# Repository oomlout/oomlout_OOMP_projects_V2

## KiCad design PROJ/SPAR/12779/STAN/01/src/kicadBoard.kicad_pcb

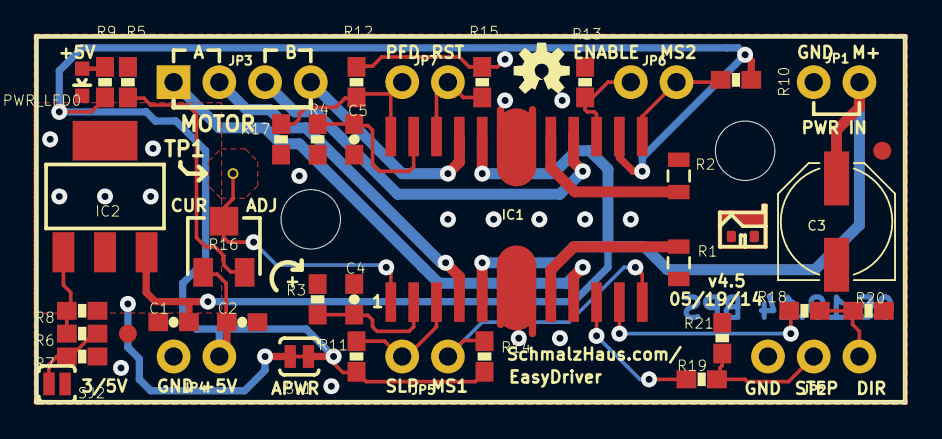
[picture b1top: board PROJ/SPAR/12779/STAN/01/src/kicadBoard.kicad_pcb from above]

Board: 2 copper layers, 48.3 x 20.3 mm, 47 parts (1 on the bottom side), 27 nets.

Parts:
C1: .1uF; 0603-CAP
C2: 1uf; 0603-CAP
C3: 47uF; PANASONIC_D
C4, C5: 680pF; 0603-CAP
FID1, FID2: FIDUCIAL1X2; FIDUCIAL-1X2
FRAME2: FRAME-LETTER; CREATIVE_COMMONS
IC1: A3967SLB; SO24W
IC2: V_REG_317SMD; SOT223
JP1, JP4, JP5, JP6, JP7: 1X02_NO_SILK
JP2: 1X03_NO_SILK
JP3: 1X04_NO_SILK
JP8, JP9: STAND-OFF
LOGO1: OSHW-LOGOS; OSHW-LOGO-S
PWR_LED0: YELLOW; LED-0603
R1, R2: .75; 0805
R3, R4: 20K; 0603-RES
R5: 2.49K; 0603-RES
R6: 390; 0603-RES
R7: 330; 0603-RES
R8: 240; 0603-RES
R9, R18, R19: 1K; 0603-RES
R10, R11, R12, R13, R14, R15, R20, R21: 10K; 0603-RES
R16: 10K; TRIMPOT-3MM-2
R17: 6.8K; 0603-RES
SJ1: SOLDERJUMPERTRACE; SJ_2S-TRACE
SJ2: SOLDERJUMPERNO; SJ_2S-NO
TP1: TEST-POINTTP_15TH_THRU; TP_15TH
U$1: SCHMALZHAUS_SMALL
U$2: LOGO-SFENEW; SFE-NEW-WEBLOGO

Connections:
5V_ALT: IC2.2, IC2.4, R8.2, SJ1.1
DIR: IC1.11, R18.1
DIR_IN: JP2.3, R18.2, R20.2
ENABLE: IC1.15, JP6.1, R13.2
GND: C1.2, C2.2, C3.-, C4.2, C5.2, IC1.6, IC1.7, IC1.18, IC1.19, JP1.1, JP2.1, JP4.2, PWR_LED0.C, R1.1, R2.1, R3.1, R4.1, R5.1, R7.1, R13.1, R17.1, R20.1, R21.1, SJ2.2
MS1: IC1.12, JP5.1, R14.1
MS2: IC1.13, JP6.2, R10.1
unnamed: IC1.8, R1.2
unnamed: PWR_LED0.A, R9.1
unnamed: IC1.17, R2.2
unnamed: R6.1, R7.2, SJ2.1
unnamed: C4.1, IC1.2, R3.2
unnamed: IC2.1, R6.2, R8.1
unnamed: C5.1, IC1.23, R4.2
unnamed: R5.2, R16.3
OUT1A: IC1.16, JP3.3
OUT1B: IC1.21, JP3.4
OUT2A: IC1.9, JP3.1
OUT2B: IC1.4, JP3.2
PFD: IC1.24, JP7.1, R12.1, R17.2
RESET: IC1.22, JP7.2, R15.1
SLEEP: IC1.3, JP5.2, R11.1
STEP: IC1.10, R19.1
STEP_IN: JP2.2, R19.2, R21.2
V+: C1.1, C3.+, IC1.5, IC1.20, IC2.3, JP1.2
VCC: C2.1, IC1.14, JP4.1, R9.2, R10.2, R11.2, R12.2, R14.2, R15.2, R16.1, SJ1.2
VREF: IC1.1, R16.2, TP1.P$1

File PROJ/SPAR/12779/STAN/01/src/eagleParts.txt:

Partlist

Exported from boardEagle.brd at 18/08/2022 15:58

EAGLE Version 9.6.2 Copyright (c) 1988-2020 Autodesk, Inc.

Assembly variant: 

Part     Value                  Package       Library                    Position (inch)       Orientation

C1       .1uF                   0603-CAP      SparkFun-Capacitors        (0.3 0.175)           R180
C2       1uf                    0603-CAP      SparkFun-Capacitors        (0.45 0.175)          R0
C3       47uF                   PANASONIC_D   rcl                        (1.75 0.395)          R90
C4       680pF                  0603-CAP      SparkFun-Capacitors        (0.695 0.225)         R90
C5       680pF                  0603-CAP      SparkFun-Capacitors        (0.695 0.575)         R270
FID1     FIDUCIAL1X2            FIDUCIAL-1X2  SparkFun-Aesthetics        (1.85 0.55)           R0
FID2     FIDUCIAL1X2            FIDUCIAL-1X2  SparkFun-Aesthetics        (0.2 0.15)            R0
IC1      A3967SLB               SO24W         Allegro                    (1.05 0.4)            R0
IC2      V_REG_317SMD           SOT223        SparkFun03_30_09           (0.15 0.45)           R0
JP1                             1X02_NO_SILK  SparkFun                   (1.7 0.7)             R0
JP2                             1X03_NO_SILK  SparkFun                   (1.6 0.1)             R0
JP3                             1X04_NO_SILK  SparkFun                   (0.3 0.7)             R0
JP4                             1X02_NO_SILK  SparkFun                   (0.4 0.1)             R180
JP5                             1X02_NO_SILK  SparkFun                   (0.9 0.1)             R180
JP6                             1X02_NO_SILK  SparkFun                   (1.3 0.7)             R0
JP7                             1X02_NO_SILK  SparkFun                   (0.8 0.7)             R0
PWR_LED  YELLOW                 LED-0603      SparkFun-LED               (0.1 0.7)             R180
R1       .75                    0805          SparkFun-Resistors         (1.405 0.305)         R90
R2       .75                    0805          SparkFun-Resistors         (1.405 0.495)         R270
R3       20K                    0603-RES      SparkFun-Resistors         (0.615 0.225)         R270
R4       20K                    0603-RES      SparkFun-Resistors         (0.615 0.575)         R90
R5       2.49K                  0603-RES      SparkFun-Resistors         (0.2 0.7)             R270
R6       390                    0603-RES      SparkFun-Resistors         (0.1 0.15)            R180
R7       330                    0603-RES      SparkFun-Resistors         (0.1 0.1)             R180
R8       240                    0603-RES      SparkFun-Resistors         (0.1 0.2)             R0
R9       1K                     0603-RES      SparkFun-Resistors         (0.15 0.7)            R270
R10      10K                    0603-RES      SparkFun-Resistors         (1.53 0.705)          R0
R11      10K                    0603-RES      SparkFun-Resistors         (0.7 0.1)             R270
R12      10K                    0603-RES      SparkFun-Resistors         (0.7 0.7)             R90
R13      10K                    0603-RES      SparkFun-Resistors         (1.2 0.7)             R270
R14      10K                    0603-RES      SparkFun-Resistors         (0.98 0.1)            R270
R15      10K                    0603-RES      SparkFun-Resistors         (0.975 0.7)           R90
R16      10K                    TRIMPOT-3MM-2 SparkFun-Electromechanical (0.41 0.34)           R0
R17      6.8K                   0603-RES      SparkFun-Resistors         (0.535 0.575)         R90
R18      1K                     0603-RES      SparkFun-Resistors         (1.68 0.2)            R0
R19      1K                     0603-RES      SparkFun-Resistors         (1.455 0.05)          R0
R20      10K                    0603-RES      SparkFun-Resistors         (1.82 0.2)            R180
R21      10K                    0603-RES      SparkFun-Resistors         (1.5 0.14)            R270
SJ1      SOLDERJUMPERTRACE      SJ_2S-TRACE   SparkFun03_30_09           (0.575 0.1)           R0
SJ2      SOLDERJUMPERNO         SJ_2S-NO      SparkFun03_30_09           (0.045 0.04)          R0
TP1      TEST-POINTTP_15TH_THRU TP_15TH       SparkFun-Passives          (0.43 0.5)            R0

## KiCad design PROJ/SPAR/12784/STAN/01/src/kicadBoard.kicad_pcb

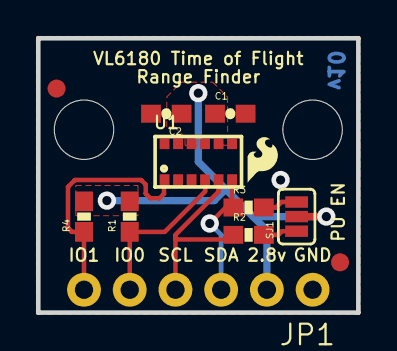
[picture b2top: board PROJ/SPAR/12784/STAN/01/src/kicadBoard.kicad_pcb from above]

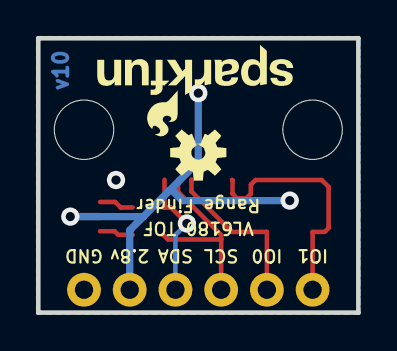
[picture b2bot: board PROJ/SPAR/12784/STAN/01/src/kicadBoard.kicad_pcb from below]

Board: 2 copper layers, 17.8 x 15.2 mm, 17 parts (2 on the bottom side), 8 nets.

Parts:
C1: 4.7uF; 0603-CAP
C2: 0.1uF; 0603-CAP
FID1, FID2: FIDUCIAL1X2; FIDUCIAL-1X2
FRAME1: FRAME-LETTER; CREATIVE_COMMONS
JP1: 1X06
LOGO1: SFE_LOGO_NAME_FLAME.1_INCH; SFE_LOGO_NAME_FLAME_.1
LOGO2: OSHW-LOGOS; OSHW-LOGO-S
R1, R4: 47K; 0603-RES
R2, R3: 2.2k; 0603-RES
SJ1: PAD-JUMPER-3-NC_BY_PASTE_YES_SILK_FULL_BOX
STANDOFF1, STANDOFF2: STAND-OFF
U1: VL6180
U$2: SFE_LOGO_FLAME_.1

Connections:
2.8V: C1.1, C2.1, JP1.2, R1.2, R4.2, SJ1.2, U1.8, U1.10
GND: C1.2, C2.2, JP1.1, U1.9, U1.12
GPIO0: JP1.5, R1.1, U1.4
GPIO1: JP1.6, R4.1, U1.1
unnamed: R2.2, SJ1.1
unnamed: R3.2, SJ1.3
SCL: JP1.4, R2.1, U1.5
SDA: JP1.3, R3.1, U1.6

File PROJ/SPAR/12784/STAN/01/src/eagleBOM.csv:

"Part";"Value";"Device";"Package";"Description";"PROD_ID";"VALUE";
"C1";"4.7uF";"4.7UF-6.3V-10%(0603)0603";"0603-CAP";"CAP-08280";"CAP-08280";"4.7uF";
"C2";"0.1uF";"0.1UF-25V(+80/-20%)(0603)";"0603-CAP";"CAP-00810";"CAP-00810";"0.1uF";
"FID1";"FIDUCIAL1X2";"FIDUCIAL1X2";"FIDUCIAL-1X2";"Fiducial Alignment Points";"";"";
"FID2";"FIDUCIAL1X2";"FIDUCIAL1X2";"FIDUCIAL-1X2";"Fiducial Alignment Points";"";"";
"FRAME1";"FRAME-LETTER";"FRAME-LETTER";"CREATIVE_COMMONS";"Schematic Frame";"";"";
"JP1";"";"M06SIP";"1X06";"Header 6";"";"";
"LOGO1";"SFE_LOGO_NAME_FLAME.1_INCH";"SFE_LOGO_NAME_FLAME.1_INCH";"SFE_LOGO_NAME_FLAME_.1";"SFE Logo, name and flame";"";"";
"LOGO2";"OSHW-LOGOS";"OSHW-LOGOS";"OSHW-LOGO-S";"Open Source Hardware Logo This logo indicates the piece of hardware it is found on incorporates a OSHW license and/or adheres to the definition of open source hardware found here: http://freedomdefined.org/OSHW";"";"";
"R1";"47K";"47KOHM1/10W1%(0603)";"0603-RES";"RES-07871";"RES-07871";"47K";
"R2";"2.2k";"2.2KOHM1/10W1%(0603)";"0603-RES";"RES-08272";"RES-08272";"2.2k";
"R3";"2.2k";"2.2KOHM1/10W1%(0603)";"0603-RES";"RES-08272";"RES-08272";"2.2k";
"R4";"47K";"47KOHM1/10W1%(0603)";"0603-RES";"RES-07871";"RES-07871";"47K";
"SJ1";"";"JUMPER-PAD-3-NC_BY_PASTE";"PAD-JUMPER-3-NC_BY_PASTE_YES_SILK_FULL_BOX";"";"";"";
"STANDOFF1";"STAND-OFF";"STAND-OFF";"STAND-OFF";"#4 Stand Off";"";"";
"STANDOFF2";"STAND-OFF";"STAND-OFF";"STAND-OFF";"#4 Stand Off";"";"";
"U1";"VL6180";"VL6180";"VL6180";"";"IC-12007";"";

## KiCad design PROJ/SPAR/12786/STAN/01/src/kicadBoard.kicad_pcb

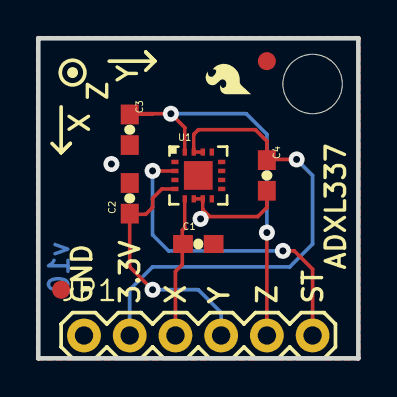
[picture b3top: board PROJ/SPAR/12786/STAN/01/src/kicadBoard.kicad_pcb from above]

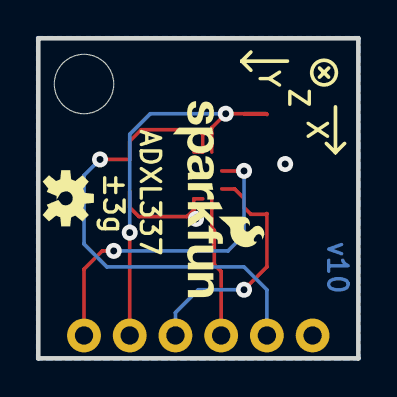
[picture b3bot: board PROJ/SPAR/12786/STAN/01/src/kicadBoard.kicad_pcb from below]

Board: 2 copper layers, 17.8 x 17.8 mm, 13 parts (2 on the bottom side), 6 nets.

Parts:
C1, C2, C3: 10nF; 0603-CAP
C4: 0.1uF; 0603-CAP
FID1, FID2: FIDUCIAL1X2; FIDUCIAL-1X2
FRAME1: FRAME-LETTER; CREATIVE_COMMONS
JP1: 1X06
LOGO1: SFE_LOGO_FLAME.1_INCH; SFE_LOGO_FLAME_.1
LOGO2: OSHW-LOGOS; OSHW-LOGO-S
LOGO3: SFE_LOGO_NAME_FLAME.1_INCH; SFE_LOGO_NAME_FLAME_.1
STANDOFF1: STAND-OFF
U1: ADXL337; LFCSP_LQ-16

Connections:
3.3V: C4.1, JP1.2, U1.14, U1.15
GND: C1.2, C2.2, C3.2, C4.2, JP1.1, U1.6, U1.7
ST: JP1.6, U1.2
X: C1.1, JP1.3, U1.5
Y: C2.1, JP1.4, U1.4
Z: C3.1, JP1.5, U1.16

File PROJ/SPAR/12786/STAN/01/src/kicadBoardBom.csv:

"Id";"Designator";"Package";"Quantity";"Designation";"Supplier and ref";
1;"STANDOFF1";"STAND-OFF";1;"STAND-OFF";;;
2;"C4";"0603-CAP";1;"0.1uF";;;
3;"LOGO1";"SFE_LOGO_FLAME_.1";1;"SFE_LOGO_FLAME.1_INCH";;;
4;"C2,C1,C3";"0603-CAP";3;"10nF";;;
5;"FID2,FID1";"FIDUCIAL-1X2";2;"FIDUCIAL1X2";;;
6;"FRAME1";"CREATIVE_COMMONS";1;"FRAME-LETTER";;;
7;"U1";"LFCSP_LQ-16";1;"ADXL337";;;
8;"JP1";"1X06";1;"";;;
9;"LOGO2";"OSHW-LOGO-S";1;"OSHW-LOGOS";;;
10;"LOGO3";"SFE_LOGO_NAME_FLAME_.1";1;"SFE_LOGO_NAME_FLAME.1_INCH";;;

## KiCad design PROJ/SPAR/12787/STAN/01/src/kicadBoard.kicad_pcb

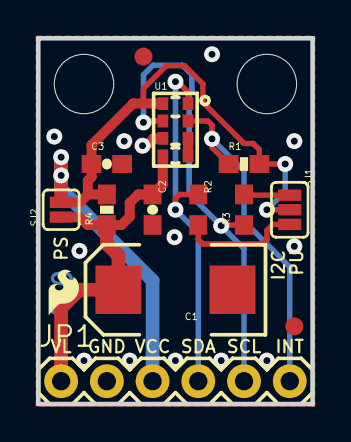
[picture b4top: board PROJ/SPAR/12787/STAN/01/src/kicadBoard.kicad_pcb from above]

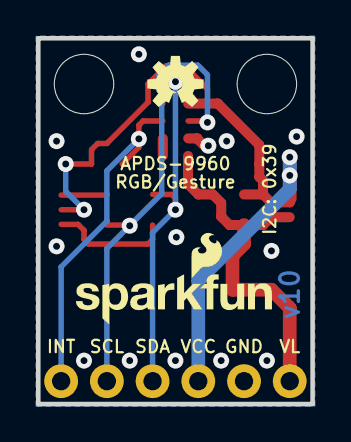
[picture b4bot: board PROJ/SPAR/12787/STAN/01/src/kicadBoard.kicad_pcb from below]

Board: 4 copper layers, 15.2 x 20.3 mm, 19 parts (2 on the bottom side), 9 nets.

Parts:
C1: 100uF; EIA7343
C2, C3: 1.0uF; 0603-CAP
FID1, FID2: FIDUCIAL1X2; FIDUCIAL-1X2
FRAME1: FRAME-LETTER; CREATIVE_COMMONS
JP1: 1X06
LOGO1: SFE_LOGO_FLAME.1_INCH; SFE_LOGO_FLAME_.1
LOGO2: OSHW-LOGOS; OSHW-LOGO-S
R1: 10k; 0603-RES
R2, R3: 4.7k; 0603
R4: DNP; 0603-RES
SJ1: SJ_3_PASTE1&2&3
SJ2: SOLDERJUMPERNC; SJ_2S
STANDOFF1, STANDOFF2: STAND-OFF
U1: APDS-9960
U$1: SFE_LOGO_NAME_FLAME.1_INCH; SFE_LOGO_NAME_FLAME_.1

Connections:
GND: C1.C, C2.2, C3.2, JP1.2, U1.6
INT: JP1.6, R1.1, U1.2
unnamed: R2.2, SJ1.3
unnamed: R3.2, SJ1.1
unnamed: U1.3, U1.4
SCL: JP1.5, R3.1, U1.7
SDA: JP1.4, R2.1, U1.1
VCC: C3.1, JP1.3, R1.2, R4.2, SJ1.2, SJ2.2, U1.8
VL: C1.A, C2.1, JP1.1, R4.1, SJ2.1, U1.5

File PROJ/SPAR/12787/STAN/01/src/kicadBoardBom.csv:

"Id";"Designator";"Package";"Quantity";"Designation";"Supplier and ref";
1;"U1";"APDS-9960";1;"APDS-9960";;;
2;"R4";"0603-RES";1;"DNP";;;
3;"SJ2";"SJ_2S";1;"SOLDERJUMPERNC";;;
4;"FRAME1";"CREATIVE_COMMONS";1;"FRAME-LETTER";;;
5;"R2,R3";"0603";2;"4.7k";;;
6;"C1";"EIA7343";1;"100uF";;;
7;"C2,C3";"0603-CAP";2;"1.0uF";;;
8;"FID1,FID2";"FIDUCIAL-1X2";2;"FIDUCIAL1X2";;;
9;"STANDOFF1,STANDOFF2";"STAND-OFF";2;"STAND-OFF";;;
10;"R1";"0603-RES";1;"10k";;;
11;"LOGO1";"SFE_LOGO_FLAME_.1";1;"SFE_LOGO_FLAME.1_INCH";;;
12;"JP1";"1X06";1;"";;;
13;"SJ1";"SJ_3_PASTE1&2&3";1;"";;;
14;"LOGO2";"OSHW-LOGO-S";1;"OSHW-LOGOS";;;
15;"U$1";"SFE_LOGO_NAME_FLAME_.1";1;"SFE_LOGO_NAME_FLAME.1_INCH";;;

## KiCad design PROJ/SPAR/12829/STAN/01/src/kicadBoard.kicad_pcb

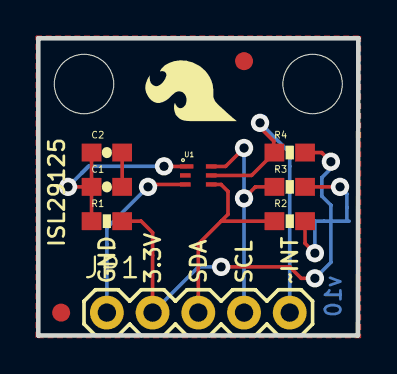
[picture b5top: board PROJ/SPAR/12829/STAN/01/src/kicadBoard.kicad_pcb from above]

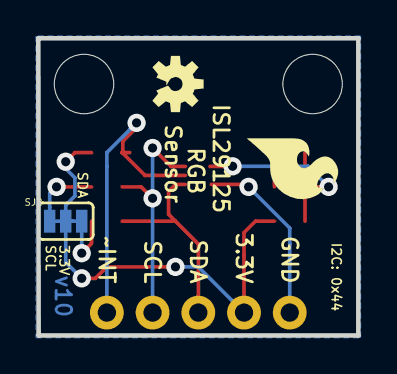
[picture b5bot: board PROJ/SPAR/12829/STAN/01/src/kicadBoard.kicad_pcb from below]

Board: 2 copper layers, 17.8 x 16.5 mm, 17 parts (3 on the bottom side), 8 nets.

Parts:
C1: 0.1uF; 0603-CAP
C2: 1.0uF; 0603-CAP
FID1, FID2: FIDUCIAL1X2; FIDUCIAL-1X2
FRAME1: FRAME-LETTER; CREATIVE_COMMONS
JP1: 1X05
LOGO2, LOGO4: SFE_LOGO_FLAME.2_INCH; SFE_LOGO_FLAME_.2
LOGO3: OSHW-LOGOS; OSHW-LOGO-S
R1: 100; 0603-RES
R2, R3, R4: 10K; 0603-RES
SJ2: SJ_3
STANDOFF1, STANDOFF2: STAND-OFF
U1: ISL29125; ODFN-LD-6

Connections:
3.3V: JP1.2, R1.2, R4.2, SJ2.2
GND: C1.2, C2.2, JP1.1, U1.3
unnamed: C1.1, C2.1, R1.1, U1.1
unnamed: R2.2, SJ2.3
unnamed: R3.2, SJ2.1
SCL: JP1.4, R3.1, U1.6
SDA: JP1.3, R2.1, U1.4
~INT: JP1.5, R4.1, U1.5

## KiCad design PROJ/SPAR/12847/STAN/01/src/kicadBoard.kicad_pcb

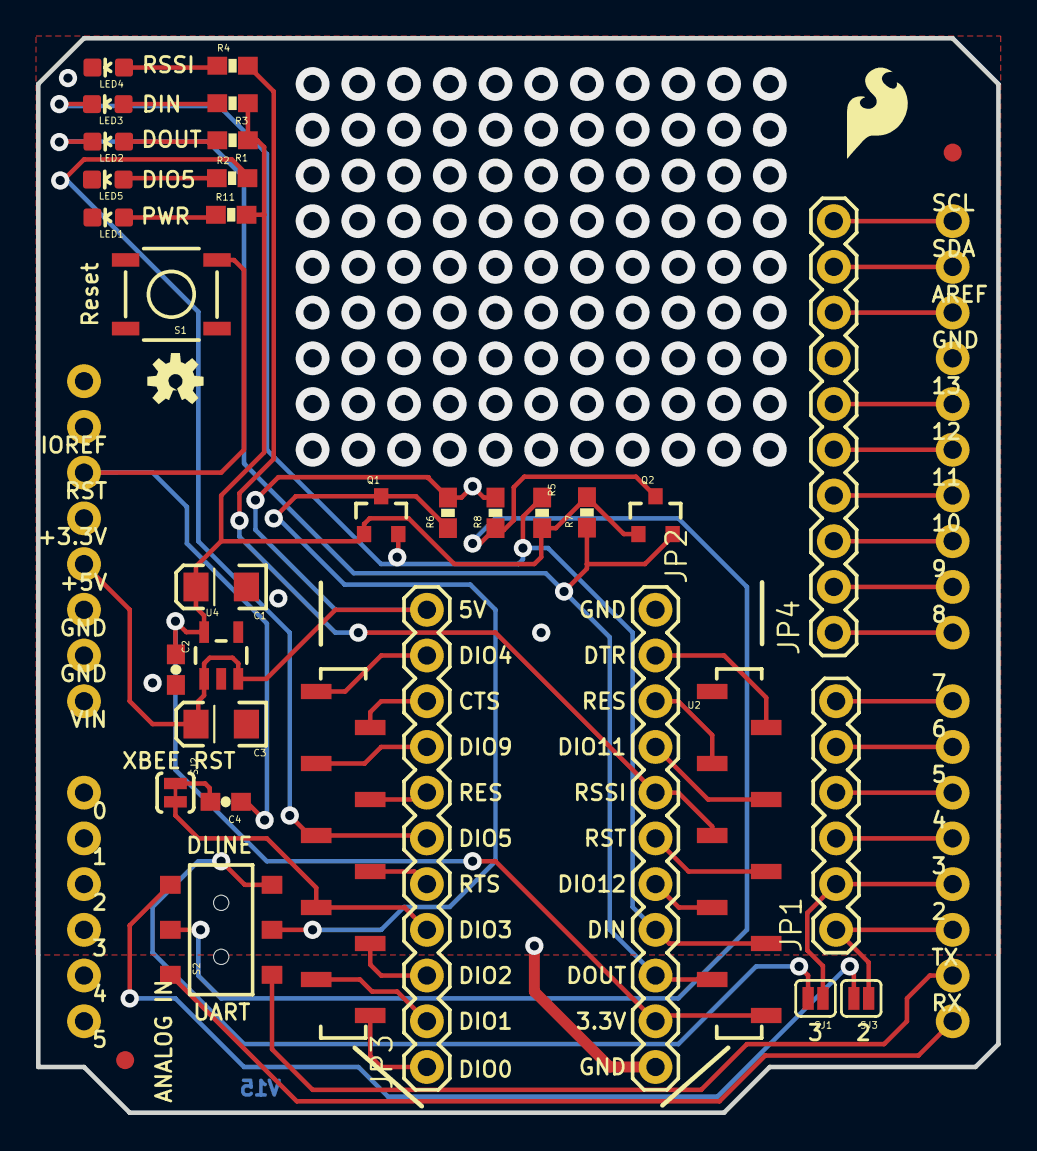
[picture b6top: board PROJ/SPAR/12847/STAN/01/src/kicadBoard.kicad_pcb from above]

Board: 2 copper layers, 53.3 x 59.7 mm, 38 parts (1 on the bottom side), 49 nets.

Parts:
C1, C3: 10uF; EIA3216
C2, C4: 0.1uF; 0603-CAP
FRAME1: FRAME-LETTER; CREATIVE_COMMONS
JP1: 1X06
JP2, JP3: M11PTH; 1X11
JP4: 1X10
JP5, JP6: FIDUCIAL1X2; FIDUCIAL-1X2
JP7: LOGO-SFENEW; SFE-NEW-WEBLOGO
LED1, LED2: Red; LED-0603
LED3, LED4, LED5: Green; LED-0603
Q1, Q2: MOSFET-NCHANNELSMD; SOT23-3
R1, R2, R3, R4, R5, R6, R7, R8, R11: 1k; 0603-RES
S1: SWITCH-MOMENTARY-2SMD; TACTILE_SWITCH_SMD
S2: SWITCH-DPDTSMD; AYZ0202
SJ1: D_TX; SJ_2S
SJ2: SOLDERJUMPERTRACE; SJ_2S-TRACE
SJ3: D_RX; SJ_2S
U1: ARDUINO_SHIELD; UNO_R3_SHIELD
U2: XBEE-1B3; XBEE-SMD
U4: V_REG_LDOSMD; SOT23-5
U$1: SFE_LOGO_FLAME_.2
U$8: OSHW-LOGOS; OSHW-LOGO-S

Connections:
3.3V: C1.A, C2.1, JP2.10, Q1.1, Q2.1, R1.1, R3.1, R5.2, R7.2, R11.2, U2.1, U4.5
5V: C3.A, JP3.11, R6.2, R8.2, U1.5V, U4.1, U4.3
AREF: JP4.8, U1.AREF
CTS: JP3.9, U2.12
DIN: JP2.8, LED3.C, Q1.2, R5.1, U2.3
DIO0: JP3.1, U2.20
DIO1: JP3.2, U2.19
DIO2: JP3.3, U2.18
DIO3: JP3.4, SJ2.2, U2.17
DIO4: JP3.10, U2.11
DIO5: JP3.6, R2.2, U2.15
DIO9: JP3.8, U2.13
DIO11: JP2.4, U2.7
DIO12: JP2.7, U2.4
DOUT: JP2.9, LED2.C, Q2.2, R7.1, U2.2
DTR: JP2.2, U2.9
D_RX: JP1.1, SJ3.1, U1.D2
D_TX: JP1.2, SJ1.1, U1.D3
GND: C1.C, C2.2, C3.C, JP2.1, JP2.11, JP4.7, LED1.C, LED4.C, LED5.C, S1.1, U1.GND@0, U1.GND@1, U1.GND@2, U2.10, U4.2
IN: Q1.3, R6.1, S2.5
unnamed: LED2.A, R1.2
unnamed: LED4.A, R4.1
unnamed: JP4.6, U1.D13
unnamed: LED3.A, R3.2
unnamed: C4.2, SJ2.1
unnamed: JP4.9, U1.SDA
unnamed: JP4.10, U1.SCL
unnamed: JP4.1, U1.D8
unnamed: JP4.2, U1.D9
unnamed: JP4.3, U1.D10
unnamed: LED1.A, R11.1
unnamed: JP4.4, U1.D11
unnamed: JP4.5, U1.D12
unnamed: LED5.A, R2.1
unnamed: S2.6, SJ1.2
unnamed: S2.3, SJ3.2
unnamed: JP1.3, U1.D4
unnamed: JP1.4, U1.D5
unnamed: JP1.5, U1.D6
unnamed: JP1.6, U1.D7
OUT: Q2.3, R8.1, S2.2
RES1: JP2.3, U2.8
RES2: JP3.7, U2.14
RESET: JP2.6, U2.5
RSSI: JP2.5, R4.2, U2.6
RST: C4.1, S1.3, U1.RES
RTS: JP3.5, U2.16
UART_RX: S2.1, U1.RX
UART_TX: S2.4, U1.TX

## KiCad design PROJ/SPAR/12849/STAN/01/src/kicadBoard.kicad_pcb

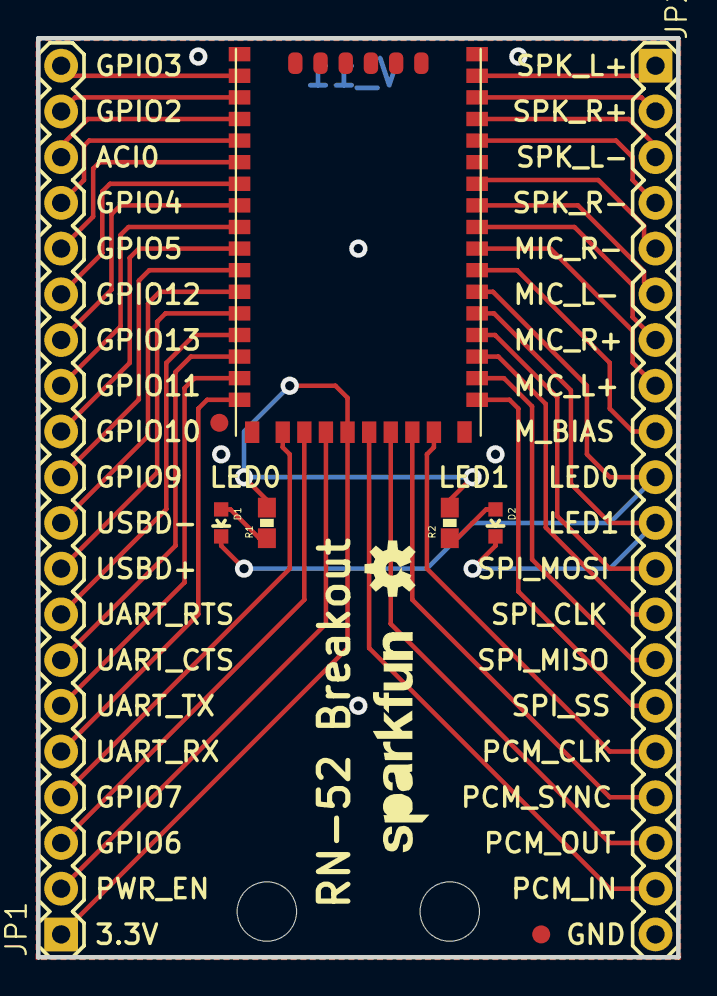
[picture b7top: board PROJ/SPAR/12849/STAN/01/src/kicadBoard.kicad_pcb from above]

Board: 2 copper layers, 35.6 x 51.1 mm, 15 parts (1 on the bottom side), 42 nets.

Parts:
D1: GREEN; LED-0603
D2: RED; LED-0603
FID1, FID2: FIDUCIAL1X2; FIDUCIAL-1X2
FRAME1: FRAME-LETTER; CREATIVE_COMMONS
JP1, JP2: M20; 1X20
LOGO1: OSHW-LOGOS; OSHW-LOGO-S
LOGO3: LOGO-SFENEW; SFE-NEW-WEBLOGO
LOGO4: LOGO-SFENW2; SFE-NEW-WEB
R1, R2: 330; 0603-RES
STANDOFF1, STANDOFF2: STAND-OFF
U1: BLUETOOTH-RN-52; RN-52

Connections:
3.3V: JP1.1, R1.2, R2.2, U1.20
AIC0: JP1.18, U1.3
GND: JP2.20, U1.36, U1.G1, U1.G2, U1.G3, U1.G4, U1.RFG1, U1.RFG2, U1.RFG3, U1.RFG4, U1.RFG5, U1.RFG6
GPIO2: JP1.19, U1.2
GPIO3: JP1.20, U1.1
GPIO4: JP1.17, U1.4
GPIO5: JP1.16, U1.5
GPIO6: JP1.3, U1.18
GPIO7: JP1.4, U1.17
GPIO9: JP1.11, U1.10
GPIO10: JP1.12, U1.9
GPIO11: JP1.13, U1.8
GPIO12: JP1.15, U1.6
GPIO13: JP1.14, U1.7
LED0: D1.C, JP2.10, U1.30
LED1: D2.C, JP2.11, U1.29
MIC_BIAS: JP2.9, U1.31
MIC_L+: JP2.8, U1.32
MIC_L-: JP2.6, U1.34
MIC_R+: JP2.7, U1.33
MIC_R-: JP2.5, U1.35
unnamed: D2.A, R2.1
unnamed: D1.A, R1.1
PCM_CLK: JP2.16, U1.24
PCM_IN: JP2.19, U1.21
PCM_OUT: JP2.18, U1.22
PCM_SYNC: JP2.17, U1.23
PWREN: JP1.2, U1.19
SPI_CLK: JP2.13, U1.27
SPI_MISO: JP2.14, U1.26
SPI_MOSI: JP2.12, U1.28
SPI_SS: JP2.15, U1.25
SPKR_L+: JP2.1, U1.40
SPKR_L-: JP2.3, U1.38
SPKR_R+: JP2.2, U1.39
SPKR_R-: JP2.4, U1.37
UART_CTS: JP1.7, U1.14
UART_RTS: JP1.8, U1.13
UART_RX: JP1.5, U1.16
UART_TX: JP1.6, U1.15
USBD+: JP1.9, U1.12
USBD-: JP1.10, U1.11

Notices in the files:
parts and their libraries:
HTTPS://CREATIVECOMMONS.ORG/LICENSES/BY-SA/3.0
RELEASED UNDER THE CREATIVE COMMONS ATTRIBUTION SHARE-ALIKE 3.0 LICENSE
RELEASED UNDER THE CREATIVE COMMONS ATTRIBUTION SHARE-ALIKE 4.0 LICENSE
HTTPS://CREATIVECOMMONS.ORG/LICENSES/BY-SA/4.0
HTTP://CREATIVECOMMONS.ORG/LICENSES/BY-SA/3.0
